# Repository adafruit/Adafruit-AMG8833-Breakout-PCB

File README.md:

## Adafruit AMG8833 Breakout PCB

<a href="http://www.adafruit.com/products/3538"><br/>
<a href="http://www.adafruit.com/products/3538"><br/>
Click here to purchase one from the Adafruit shop</a>

PCB files for the Adafruit AMG8833 8x8 IR sensor breakout board. Format is EagleCAD schematic and board layout

For more details, check out the product page at
* https://www.adafruit.com/products/3538

### Description

Add heat-vision to your project and with an Adafruit AMG8833 Grid-EYE Breakout! This sensor from Panasonic is an 8x8 array of IR thermal sensors. When connected to your microcontroller (or raspberry Pi) it will return an array of 64 individual infrared temperature readings over I2C. It's like those fancy thermal cameras, but compact and simple enough for easy integration.

This part will measure temperatures ranging from 0°C to 80°C (32°F to 176°F) with an accuracy of +- 2.5°C (4.5°F). It can detect a human from a distance of up to 7 meters (23) feet. With a maximum frame rate of 10Hz, It's perfect for creating your own human detector or mini thermal camera. We have code for using this breakout on an Arduino or compatible (the sensor communicates over I2C) or on a Raspberry Pi with Python. On the Pi, with a bit of image processing help from the SciPy python library we were able to interpolate the 8x8 grid and get some pretty nice results!

The AMG8833 is the next generation of 8x8 thermal IR sensors from Panasonic, and offers higher performance than it's predecessor the AMG8831. The sensor only supports I2C, and has a configurable interrupt pin that can fire when any individual pixel goes above or below a threshold that you set.

To make it easy to use, we pick & placed it on a breakout board with a 3.3V regulator and level shifting. So you can use it with any 3V or 5V microcontroller or computer.

### License

Adafruit invests time and resources providing this open source design, please support Adafruit and open-source hardware by purchasing products from [Adafruit](https://www.adafruit.com)!

Designed by Limor Fried/Ladyada for Adafruit Industries.

Creative Commons Attribution/Share-Alike, all text above must be included in any redistribution. See license.txt for additional details.

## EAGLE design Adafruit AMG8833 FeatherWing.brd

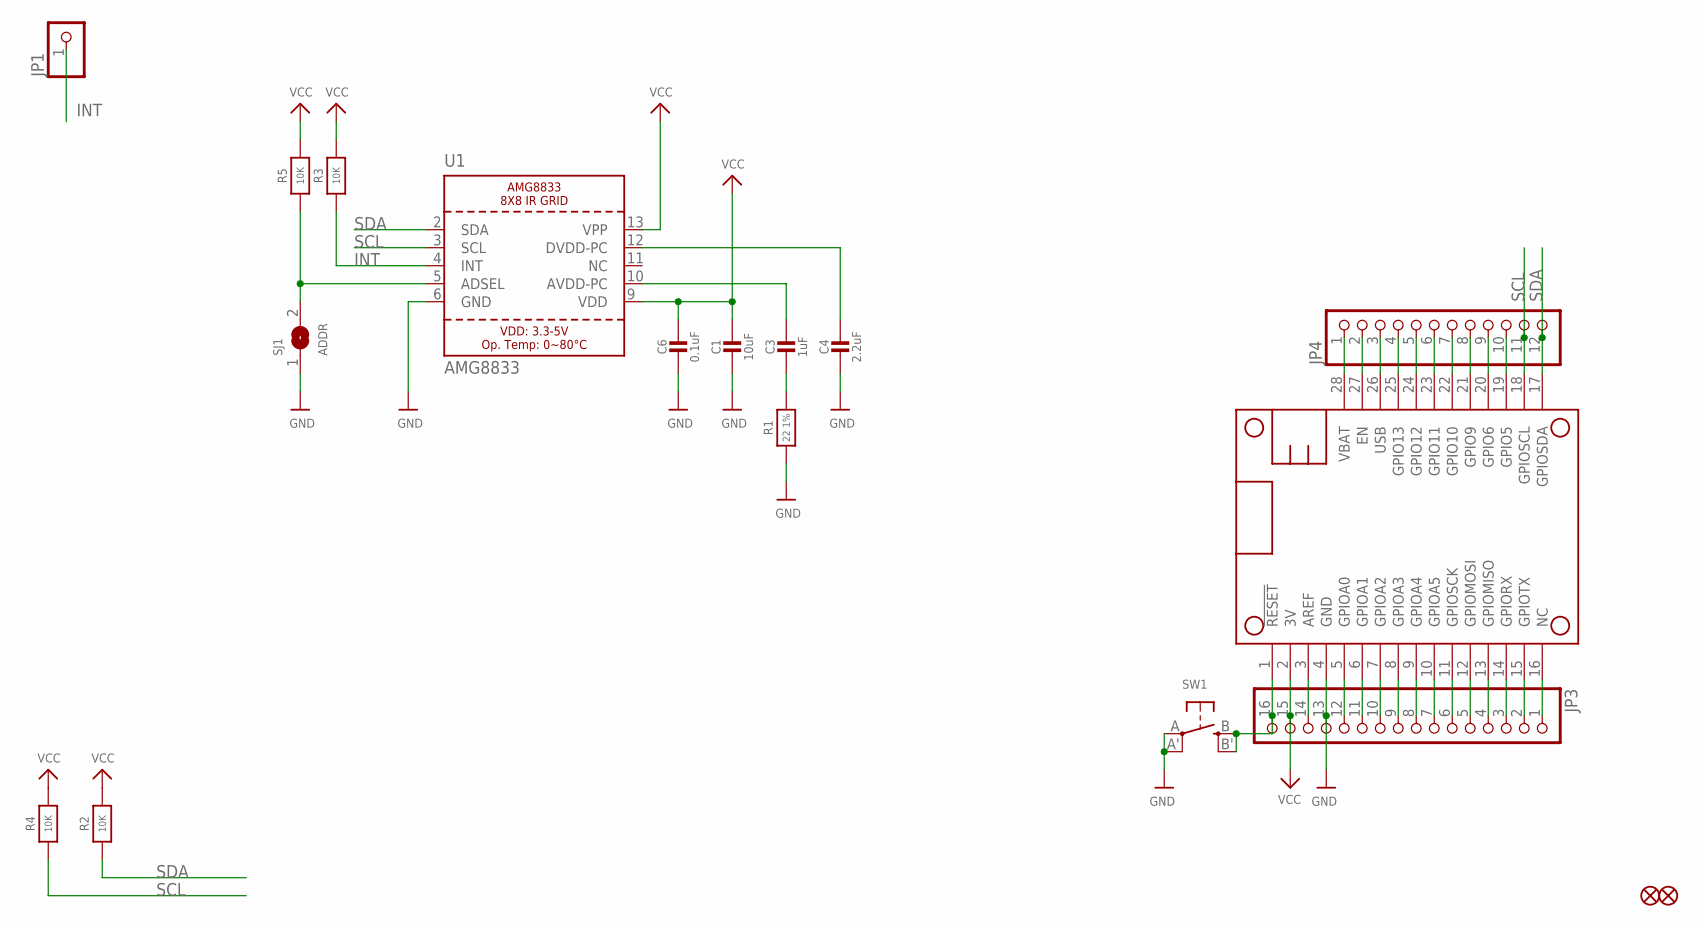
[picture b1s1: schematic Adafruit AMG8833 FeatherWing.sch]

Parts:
C1: 10uF; 0805-NO
C3: 1uF; 0805-NO
C4: 2.2uF; 0805-NO
C6: 0.1uF; 0805-NO
FID1, FID2: FIDUCIAL""; FIDUCIAL_1MM
JP1: HEADER-1X1ROUND; 1X01_ROUND
JP3: HEADER-1X16ROUND; 1X16_ROUND
JP4: HEADER-1X12; 1X12_ROUND
MS1: FEATHERWING
R1: 22 1%; 0805-NO
R2, R3, R4, R5: 10K; 0805-NO
SJ1: ADDR; SOLDERJUMPER_ARROW_NOPASTE
SW1: SWITCH_TACT_SMT4.6X2.8; BTN_KMR2_4.6X2.8
U1: AMG8833

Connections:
A: JP3.12, MS1.5 (GPIOA0)
AREF: JP3.14, MS1.3 (AREF)
AVDD-PC1: C3.1, U1.10 (AVDD-PC)
B: JP3.11, MS1.6 (GPIOA1)
C: JP3.10, MS1.7 (GPIOA2)
D: JP3.9, MS1.8 (GPIOA3)
DVDD-PC1: C4.1, U1.12 (DVDD-PC)
E: JP3.8, MS1.9 (GPIOA4)
EN: JP4.2, MS1.27 (EN)
F: JP3.7, MS1.10 (GPIOA5)
G: JP3.1, MS1.16 (NC)
GND: C1.2, C4.2, C6.2, JP3.13, MS1.4 (GND), R1.1, SJ1.1, SW1.A, SW1.A' (P1), U1.6 (GND)
H: JP4.10, MS1.19 (GPIO5)
I: JP4.9, MS1.20 (GPIO6)
INT: JP1.1, R3.1, U1.4 (INT)
J: JP4.8, MS1.21 (GPIO9)
K: JP4.7, MS1.22 (GPIO10)
L: JP4.6, MS1.23 (GPIO11)
M: JP4.5, MS1.24 (GPIO12)
MISO: JP3.4, MS1.13 (GPIOMISO)
MOSI: JP3.5, MS1.12 (GPIOMOSI)
N: JP4.4, MS1.25 (GPIO13)
unnamed: R5.1, SJ1.2, U1.5 (ADSEL)
unnamed: C3.2, R1.2
RESET: JP3.16, MS1.1 (!RESET), SW1.B (S), SW1.B' (S1)
RX: JP3.3, MS1.14 (GPIORX)
SCK: JP3.6, MS1.11 (GPIOSCK)
SCL: JP4.11, MS1.18 (GPIOSCL), R4.1, U1.3 (SCL)
SDA: JP4.12, MS1.17 (GPIOSDA), R2.1, U1.2 (SDA)
TX: JP3.2, MS1.15 (GPIOTX)
USB: JP4.3, MS1.26 (USB)
VBAT: JP4.1, MS1.28 (VBAT)
VCC: C1.1, C6.1, JP3.15, MS1.2 (3V), R2.2, R3.2, R4.2, R5.2, U1.9 (VDD), U1.13 (VPP)

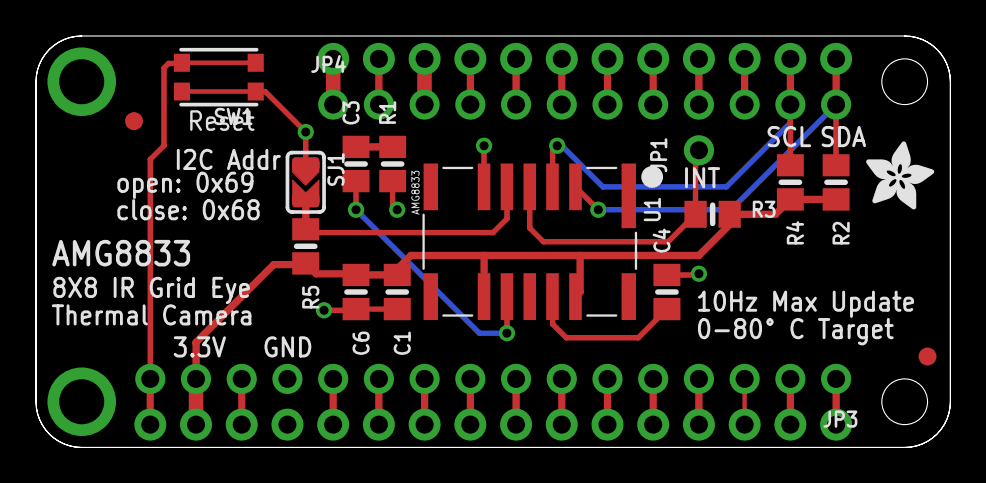
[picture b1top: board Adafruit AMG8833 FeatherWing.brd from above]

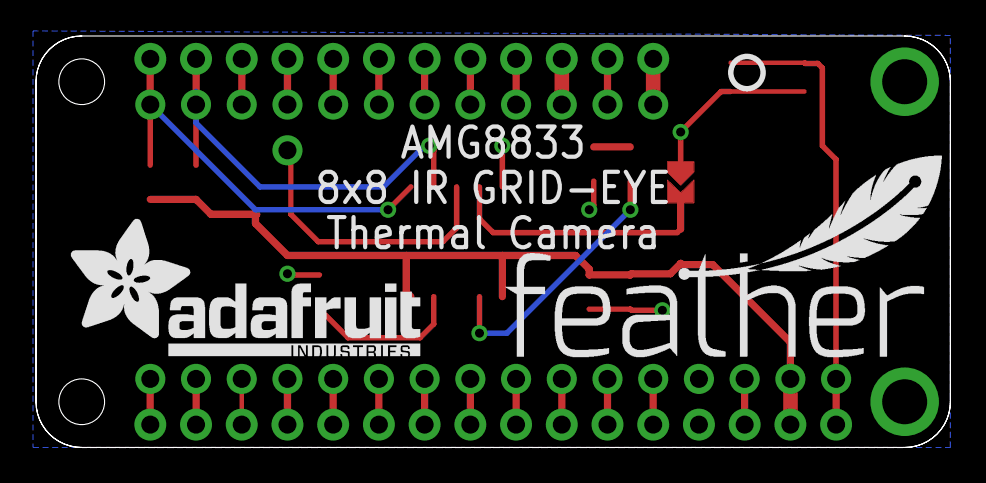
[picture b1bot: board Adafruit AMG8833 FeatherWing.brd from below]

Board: 2 copper layers, 50.8 x 22.9 mm, 22 parts (3 on the bottom side), 33 nets.

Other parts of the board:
U$2: ADAFRUIT_TEXT_20MM
U$14: ADAFRUIT_3.5MM
U$15: FEATHERLOGO
U$16: PCBFEAT-REV-040

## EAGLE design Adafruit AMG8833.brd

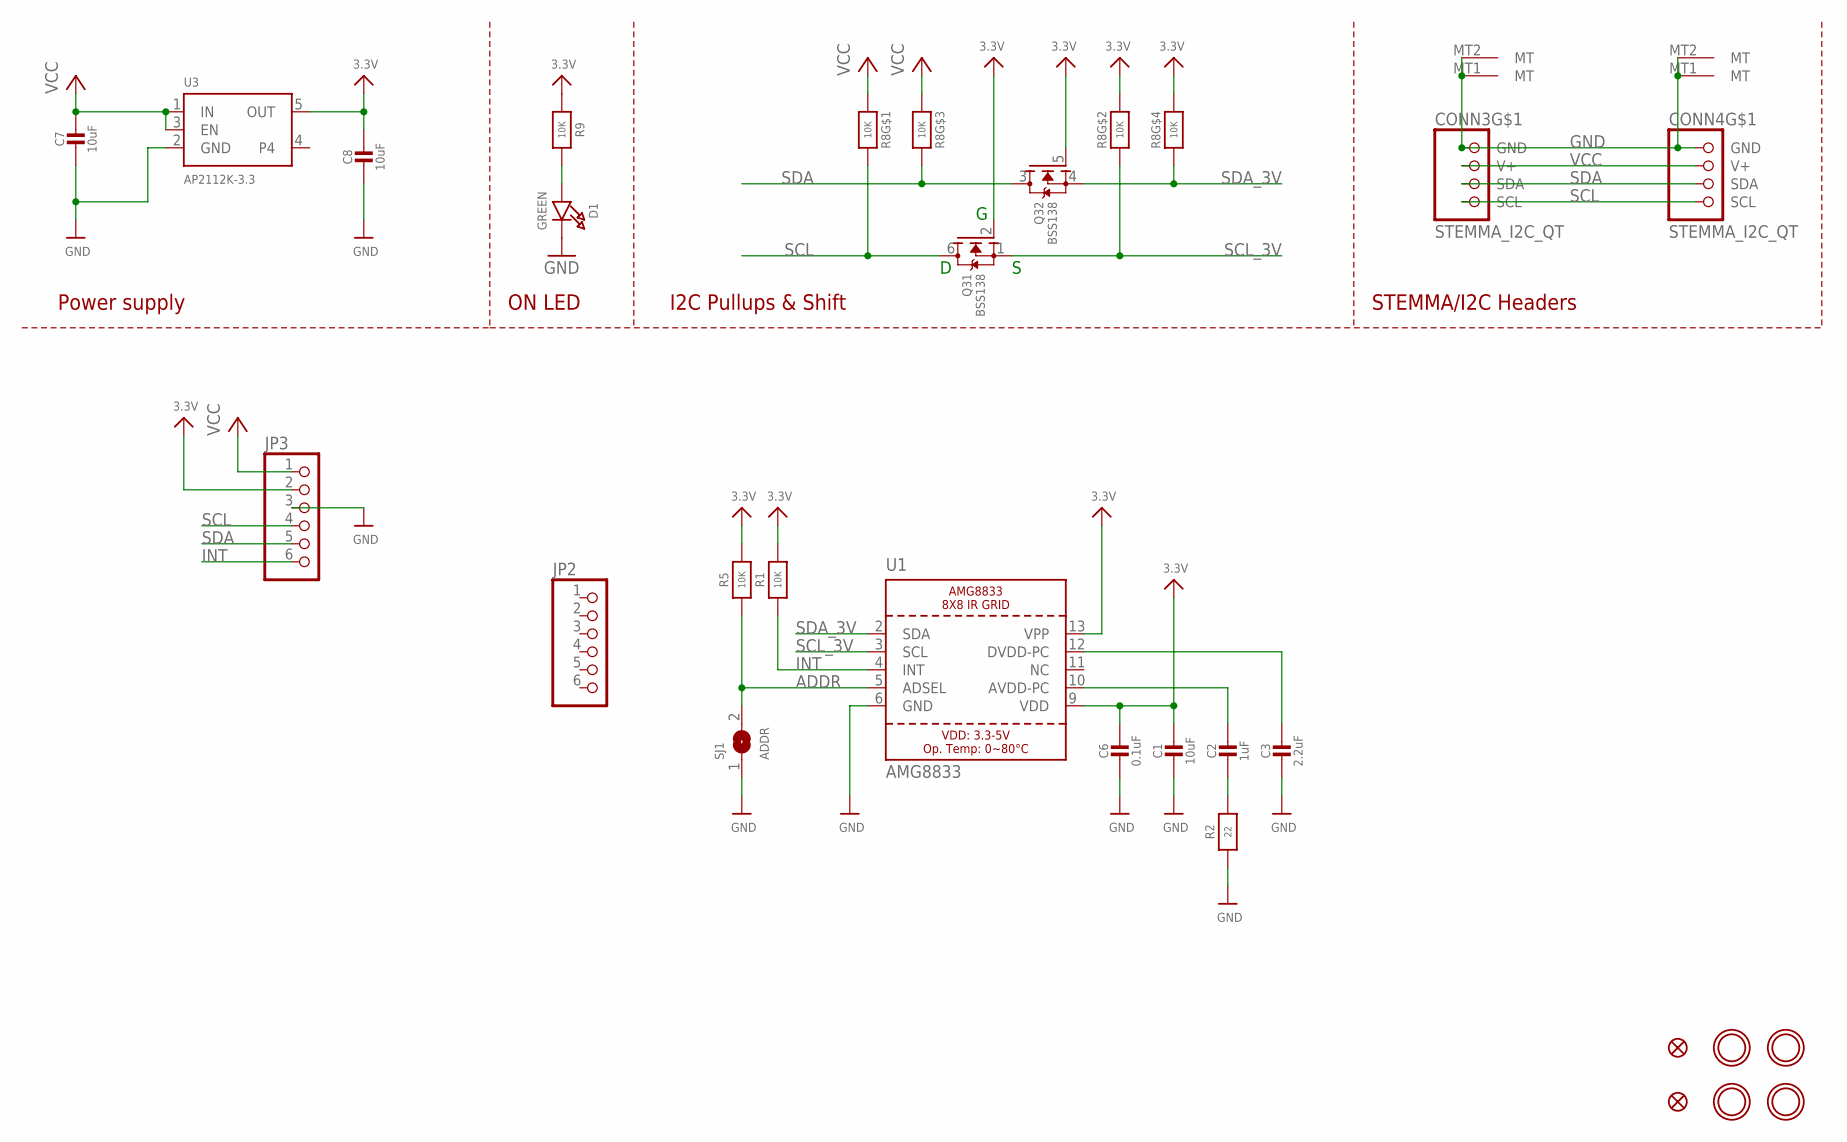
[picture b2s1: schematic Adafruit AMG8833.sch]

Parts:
C1, C7, C8: 10uF; 0805-NO
C2: 1uF; 0603-NO
C3: 2.2uF; 0805-NO
C6: 0.1uF; 0603-NO
CONN3, CONN4: STEMMA_I2C_QT; JST_SH4
D1: GREEN; CHIPLED_0603_NOOUTLINE
FID1, FID4: FIDUCIAL_1MM
JP2, JP3: HEADER-1X670MIL; 1X06_ROUND_70
Q3: BSS138; SOT363
R1, R5, R9: 10K; 0603-NO
R2: 22; 0603-NO
R8: 10K; RESPACK_4X0603
SJ1: ADDR; SOLDERJUMPER_ARROW_NOPASTE
U1: AMG8833
U3: AP2112K-3.3; SOT23-5
U$40, U$41, U$43, U$44: MOUNTINGHOLE2.5; MOUNTINGHOLE_2.5_PLATED

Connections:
3.3V: C1.1, C6.1, C8.1, JP3.2, Q3.2 (G), Q3.5 (G), R1.2, R5.2, R8.2 (1), R8.4 (1), R9.1, U1.9 (VDD), U1.13 (VPP), U3.5 (OUT)
ADDR: R5.1, SJ1.2, U1.5 (ADSEL)
AVDD-PC: C2.1, U1.10 (AVDD-PC)
DVDD-PC: C3.1, U1.12 (DVDD-PC)
GND: C1.2, C3.2, C6.2, C7.2, C8.2, CONN3.1 (GND), CONN3.MT1 (MT), CONN3.MT2 (MT), CONN4.1 (GND), CONN4.MT1 (MT), CONN4.MT2 (MT), D1.C, JP3.3, R2.1, SJ1.1, U1.6 (GND), U3.2 (GND)
INT: JP3.6, R1.1, U1.4 (INT)
unnamed: D1.A, R9.2
unnamed: C2.2, R2.2
SCL: CONN3.4 (SCL), CONN4.4 (SCL), JP3.4, Q3.6 (D), R8.8 (2)
SCL_3V: Q3.1 (S), R8.7 (2), U1.3 (SCL)
SDA: CONN3.3 (SDA), CONN4.3 (SDA), JP3.5, Q3.3 (D), R8.6 (2)
SDA_3V: Q3.4 (S), R8.5 (2), U1.2 (SDA)
VCC: C7.1, CONN3.2 (V+), CONN4.2 (V+), JP3.1, R8.1, R8.3 (1), U3.1 (IN), U3.3 (EN)

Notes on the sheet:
I2C Pullups & Shift
STEMMA/I2C Headers
ON LED
Power supply

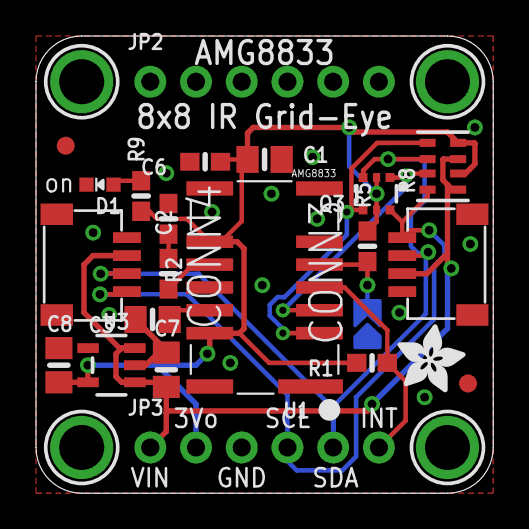
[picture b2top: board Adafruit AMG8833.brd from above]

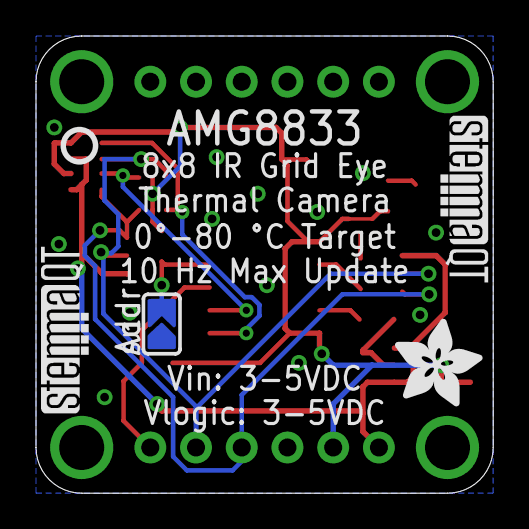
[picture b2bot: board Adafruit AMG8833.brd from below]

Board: 2 copper layers, 25.4 x 25.4 mm, 31 parts (5 on the bottom side), 13 nets.

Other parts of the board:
U$28: ADAFRUIT_5MM
U$46: ADAFRUIT_3.5MM
U$47: PCBFEAT-REV-040
U$48, U$49: STEMMAQT

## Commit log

2021-03-09 Add board files.
2021-03-09 Add asset
2021-06-08 Add FeatherWing board files.

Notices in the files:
parts and their libraries:
microbuilder: This work is placed in the public domain, and may be freely used for commercial and non-commercial work with the following conditions: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
